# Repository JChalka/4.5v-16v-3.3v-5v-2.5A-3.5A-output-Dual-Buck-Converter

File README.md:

# 4.5v-16v 3.3v/5v 2.5A/3.5A output Dual Buck Converter
 Dual Buck Converter using TPS65253

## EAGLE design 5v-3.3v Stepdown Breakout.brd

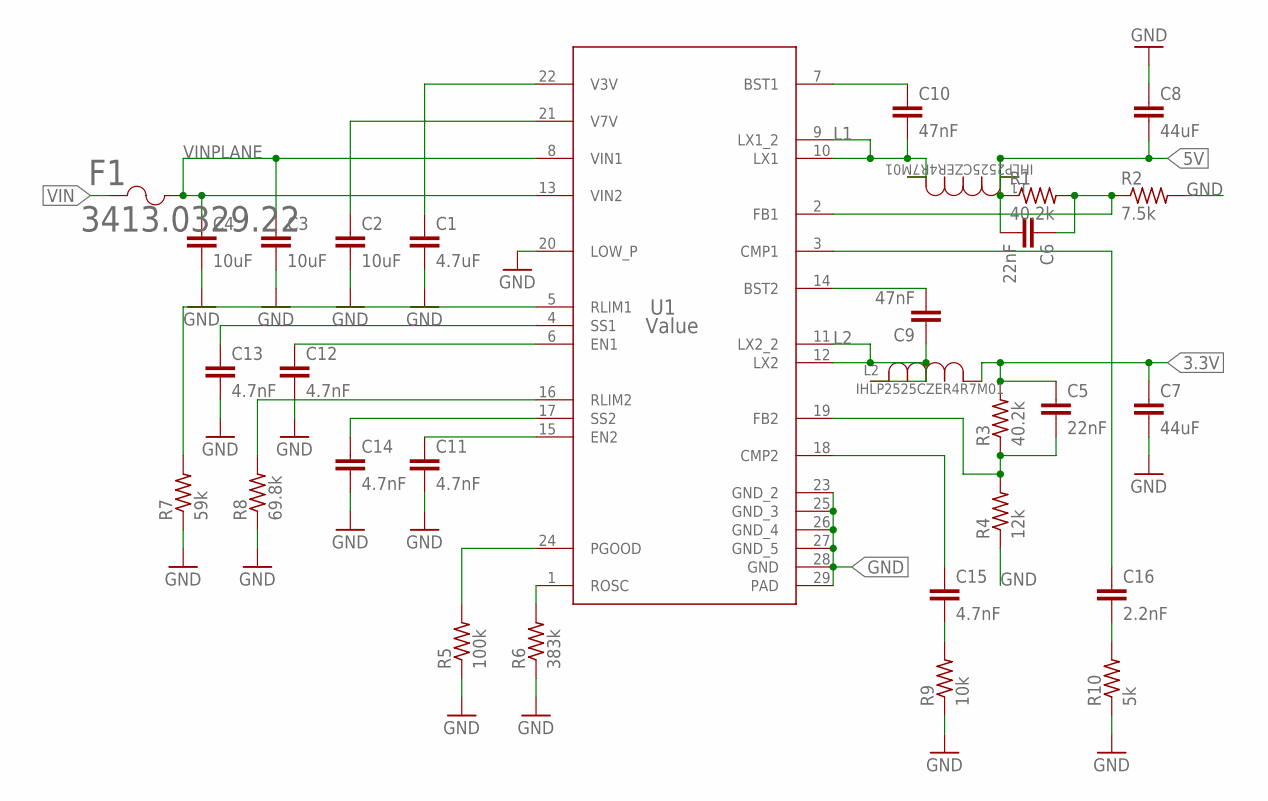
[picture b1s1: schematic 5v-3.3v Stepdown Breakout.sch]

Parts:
C1: 4.7uF; 0402-TIGHT
C2, C3, C4: 10uF; 0603
C5, C6: 22nF; 0402
C7, C8: 44uF; 0402
C9, C10: 47nF; 0402-TIGHT
C11, C12, C13, C14, C15: 4.7nF; 0402-TIGHT
C16: 2.2nF; 0402-TIGHT
F1: 3413.0329.22; FUS_SCHURTER_3413_SCH
L1, L2: IHLP2525CZER4R7M01; IND25X25CZ
R1, R3: 40.2k; R0402
R2: 7.5k; R0402
R4: 12k; R0402
R5: 100k; R0402
R6: 383k; R0402
R7: 59k; R0402
R8: 69.8k; R0402
R9: 10k; R0402
R10: 5k; R0402
U1: Value; RHD0028A

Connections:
3.3V: C5.1, C7.1, L2.1, R3.2
5V: C6.2, C8.2, L1.2, R1.1
GND: C1.2, C2.2, C3.2, C4.2, C7.2, C8.1, C11.2, C12.2, C13.2, C14.2, R2.2, R4.1, R5.1, R6.1, R7.1, R8.1, R9.1, R10.1, U1.20 (LOW_P), U1.23 (GND_2), U1.25 (GND_3), U1.26 (GND_4), U1.27 (GND_5), U1.28 (GND), U1.29 (PAD)
L1: C10.2, L1.1, U1.9 (LX1_2), U1.10 (LX1)
L2: C9.1, L2.2, U1.11 (LX2_2), U1.12 (LX2)
unnamed: C2.1, U1.21 (V7V)
unnamed: C1.1, U1.22 (V3V)
unnamed: C5.2, R3.1, R4.2, U1.19 (FB2)
unnamed: C6.1, R1.2, R2.1, U1.2 (FB1)
unnamed: C9.2, U1.14 (BST2)
unnamed: C10.1, U1.7 (BST1)
unnamed: C12.1, U1.6 (EN1)
unnamed: C11.1, U1.15 (EN2)
unnamed: R5.2, U1.24 (PGOOD)
unnamed: C14.1, U1.17 (SS2)
unnamed: R6.2, U1.1 (ROSC)
unnamed: C13.1, U1.4 (SS1)
unnamed: R8.2, U1.16 (RLIM2)
unnamed: R7.2, U1.5 (RLIM1)
unnamed: C15.2, R9.2
unnamed: C15.1, U1.18 (CMP2)
unnamed: C16.1, U1.3 (CMP1)
unnamed: C16.2, R10.2
VIN: F1.1
VINPLANE: C3.1, C4.1, F1.2, U1.8 (VIN1), U1.13 (VIN2)

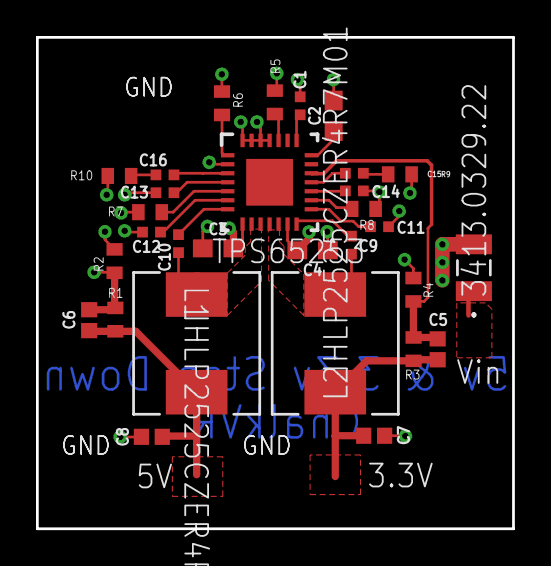
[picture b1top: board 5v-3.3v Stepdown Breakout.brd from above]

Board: 4 copper layers, 26.5 x 27.3 mm, 30 parts (0 on the bottom side), 24 nets.

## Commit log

2021-04-28 Initial Commit
    Added V1 Gerber, PCB, and Schematic files as well as the needed libraries
2021-04-28 Create LICENSE

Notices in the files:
parts and their libraries:
SparkFun-Capacitors: Licensing: Creative Commons ShareAlike 4.0 International - https://creativecommons.org/licenses/by-sa/4.0
